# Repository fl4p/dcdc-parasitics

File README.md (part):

# parasitics — KiCad → FastHenry power-stage extractor

Extracts the half-bridge power-stage parasitic inductances and resistances
from a KiCad PCB for:

1. **Switch-node ringing** — the commutation-loop inductance that,
   with the FET Coss and Qrr, sets the SW overshoot and ring frequency.
2. **Gate-drive analysis** — compute gate-loop inductance and detect ringing
   issues. The gate loop overlaps the high-di/dt commutation path through the
   FET **source lead**, so that shared **common-source inductance (CSI)** feeds
   power di/dt back into the gate drive.
3. **Power-loss / efficiency modelling** — the extracted **resistances** are the
   copper contribution to the I²R budget, split **per switch** so
   the conduction loss can be weighted by each switch's duty (HS by D, LS by 1−D —
   the LS copper dominates at low duty). The loop carries current at two very
   different frequencies (switching frequency and HF ringing), so it has [two
   resistances](#two-resistances-hf-ring-vs-lf-conduction).

You give it the **switch-node net** and the **GND net**; everything else (HS/LS
FETs, Vin rail, gate nets, input caps) is auto-discovered from connectivity, with
overrides for every guess.

## Showcase

Half-bridge parasitics extracted from the open-hardware
[LibreSolar MPPT 2420 HC](https://github.com/LibreSolar/mppt-2420-hc) (4-layer
synchronous buck), rendered by `--svg`: each parasitic as a labelled coil, the
two **common-source source-leads in red**, the input-cap bank (the ported cap and
the greyed-out ones), and the auto-detected gate network (Rg). This is the
historical lead-inclusive fixture and is retained as an output-format showcase;
its numeric labels are not a current copper-only validation.

## How it works

Each extraction basis uses one FastHenry solve with multiple ports to obtain its
full mutual-inductance matrix. The baseline/full-loop extraction and the
`lead_mm=0` identity-matrix path need one solve. A non-identity matrix Cin request
may run three matched bases (`full_loop`, `cap_only`, and `switch_residual`) so
the producer can separate cap-side and switch-side copper without mixing gauges.

| Port | Across | Gives |
|------|--------|-------|
| `P_pwr` | nearest Cin — **MLCC** (Vin ↔ GND) | commutation-loop L, HF ring R |
| `P_ghs` | HS gate driver-end ↔ HS gate return | HS gate-loop L |
| `P_gls` | LS gate driver-end ↔ LS gate return | LS gate-loop L |
| `P_bulk` | nearest **bulk electrolytic** (Vin ↔ GND) | LF conduction-loop R |
| `P_hs` | Vin(bulk) → SW, via HS leads | HS conduction R |
| `P_ls` | SW → GND(bulk), via LS leads | LS conduction R |
| `P_probe_<name>` | any declared `REF.PAD` ↔ `REF.PAD` (opt-in, see `probe_ports`) | mount-loop L/R of that position |

### Electrostatic foundation (Palace)

Palace is the primary maintained electrostatic solver. The
`palace-electrostatic-pcb-gates-v2` path uses conformal tetrahedral volume
meshes, finite closed conductor terminals, explicit air/dielectric material
volumes, and a declared outer Dirichlet boundary that approximates
electrostatic infinity. That boundary is never treated as PE, chassis, a PCB
net, or SPICE node `0`; an outer-domain expansion ladder is mandatory.

`lib/palace_mesh.py` writes the qualified Gmsh fixtures. Real PCB geometry uses
`lib/palace_plc_mesh.py`: MeshPy nodes one global planar conductor/material
arrangement, that exact arrangement is reused at every geometry z-plane, and
triangular prisms receive a deterministic conformal tetrahedral split. It
rejects open/non-manifold shells, incomplete terminal/material coverage, and
nonpositive tetrahedral Jacobians, then emits first-order Gmsh 2.2 directly.
`lib/palace_build.py` binds the pinned source patch, CMake caches,
linked libraries, launcher, wrapper, and binary. `lib/palace.py` binds those
manifests to Palace JSON configs, runs the solver, gates an independently
ordered 17-digit terminal reaction-charge Maxwell matrix against Palace's
energy matrix, and preserves exact streams, resolved config, runtime metadata,
and execution identity. The qualification build also hard-checks explicit
`||b-Ax||/||b||` after every terminal solve. Mesh,
polynomial-order, and finite-domain ladders over the frozen air, enclosed-FR4,
and PCB-like fixtures must pass before any Fugu run. See
`docs/palace-electrostatic-qualification-plan.md`.

Production launches use a content-addressed user-space execution snapshot whose
config, mesh, launcher, solver, and helper bytes are validated before and after
the process. Ordinary runs select a bounded local resource class. Checkpointed
runs additionally require a finite resource decision and a canonical E5 ledger
attempt before launch; every attempt receives a fresh snapshot/output root, and
matrices are consumable only through the terminal ledger capability.

The complete 24-rung fixture ladder has passed. `extract_palace_mesh.py` runs
the two-interpreter KiCad adapter, preserves every named net and flashed no-net
item separately, retains NPTH holes as voids rather than terminals, and binds
PCB, dump, stackup/material policy, geometry controls, mesher, and output bytes:

```sh
PYTHONPATH=out/palace-qualification/venv/lib/python3.14/site-packages \
  python3 extract_palace_mesh.py board.kicad_pcb \
  --material 'Top Solder Mask=3.3' \
  --material 'Bottom Solder Mask=3.3' \
  -o out/palace-pcb-geometry
```

Material overrides are explicit assumptions, not validated values. A physical
Fugu model still requires source-bound P2 evidence, convergence ladders,
independent review, and actual material identification or bounded sensitivity.

### Diagnostic legacy (FasterCap)

`lib/fastercap.py` provides the independent 3-D electrostatic path: it closes
conforming 2-D triangle meshes into finite-thickness conductor surfaces, emits
closed interfaces between dielectric regions, writes self-contained FasterCap
panel files, and runs the headless solver through `$FASTERCAP`. Each deck has a
hashed sidecar manifest with stable solver labels. The runner returns a Maxwell
matrix only after exact label identity, normal termination, final automatic-norm,
per-RHS GMRES, live process-tree resource, raw reciprocity/passivity, strict
post-average passivity, and exact branch-reconstruction gates pass. Complete
matrices from failed or partial runs remain diagnostic-only. Manual fixed-`-m`/
fixed-`-t` probes use a separate API and never expose a qualified matrix. The
backend-neutral `lib/maxwell.py` validates matrix symmetry/passivity, converts
`Q = C_M V` into pairwise plus reference capacitors, reconstructs the original
matrix for an exact contract check, and emits a passive SPICE subcircuit. The
runner enforces a separate per-coupling reciprocity tolerance before returning
the symmetric average; FasterCap's `-a` tolerance controls refinement
convergence and is not reused as a reciprocity bound. Every invocation preserves
byte-exact content-addressed stdout/stderr and writes either a
`rejected_diagnostic` manifest or a `numerically_converged_diagnostic` manifest
under gate policy `fastercap-pcb-gates-v1`. Diagnostic convergence is not a
physical-model qualification.

This foundation is deliberately not wired into `extract_parasitics.py` yet.
`extract_capacitance.py` provides the first two-interpreter KiCad adapter: a
stdlib-only KiCad Python step dumps exact filled-zone contours in millimetres,
then system Python uses Shapely 2.1 constrained triangulation to close grouped
copper surfaces and converts every panel coordinate to FasterCap SI metres. For
example:

```sh
python3 extract_capacitance.py board.kicad_pcb \
  --group SWITCH=SW --group RETURN=PGND,GND \
  -o out/electrostatic-geometry

# Explicit opt-in reduced diagnostic representation
python3 extract_capacitance.py board.kicad_pcb \
  --group SWITCH=SW --group RETURN=PGND,GND \
  --representation effective-thickness \
  --effective-thickness-um 34 --anchor midplane \
  -o out/electrostatic-geometry-reduced
```

Generated names encode source, representation, material scope, and lifecycle,
for example `filled_zones_physical_air_only_diagnostic.lst` and
`filled_zones_effective_34um_midplane_air_only_diagnostic.lst`. Geometry metadata
uses a canonical content hash in its filename. Its fail-closed loader verifies
the filename/content ID plus the referenced deck, deck manifest, and reduction
provenance hashes. The deck manifest binds the same reduction provenance and its
hash; solver run manifests then bind the deck manifest plus all solver settings
and streams.

Both decks are geometry-development diagnostics, **not physical PCB capacitance
models**. They exclude tracks, pads, vias, and copper graphics and do not yet emit
the parsed stackup's dielectric interfaces. The only fixture-qualified reduction
is watertight closed 35 µm to 34 µm copper, midplane anchored, for overlapping
1 mm square parallel plates in air with a 100 µm source face gap and an explicit
pinned synthetic-fixture context. The reusable API marks any PCB/Fugu2 or
full-stackup use `outside_fixture_envelope`, fixes
`physical_validation_authorized=false`, and caps its lifecycle at
`numerically_converged_diagnostic`.

The content-addressed geometry manifest records limitations, PCB and contour-dump
hashes, KiCad version/interpreter, dump record count, areas, repair counts,
simplification error, minimum boundary segment, triangle/panel counts, source and
effective thicknesses, anchor, gap/displacement errors, qualification scope, and
artifact class. Use `--geometry-tolerance` (mm, default 0.001) as an explicit
panel-convergence knob; geometry that exceeds the area-error gate is rejected.

Start solver validation with the synthetic fixture:

```sh
python3 examples/fastercap_parallel_plate.py -o out/fastercap-parallel-plate
FASTERCAP=/path/to/FasterCap \
  python3 examples/fastercap_parallel_plate.py --run \
  -o out/fastercap-parallel-plate
```

The first command only emits inspectable geometry. The second writes
`capacitance.lib` only when every `fastercap-pcb-gates-v1` solver and matrix gate
passes. Unpatched FasterCap 6.0.7 macOS builds may emit
`Error: cannot retrieve the information about the free memory quantity`; the
fail-closed runner preserves a `rejected_diagnostic` manifest and returns no
matrix for those builds. The local macOS build uses Mach VM statistics for this
resource check and passes the real parallel-plate smoke test. See
`docs/fastercap-slice1-diagnosis.md`. A solver build that terminates without
diagnostics additionally reports plate-to-plate capacitance against the ideal
estimate; fringing means the ratio is not exactly one.

In the full-loop basis, both FET channels are shorted at the die plane
(`.equiv drain_die source_die`)
and each gate is closed to its source there, so `P_pwr` traces the full
`Cin → HS → SW → LS → GND → Cin` shoot-through loop and each gate loop shares that
FET's source lead. **CSI then falls out as the side-specific mutual**
`M(P_hs, P_ghs)` / `M(P_ls, P_gls)` — the shared source-lead partial inductance
that the gate driver actually sees. The older full-loop mutual is still recorded
as `csi_hs_loop` / `csi_ls_loop` in JSON for diagnostics. Whether the gate return
taps the die-source (**Kelvin**, CSI excluded) or the power-source pad
(**non-Kelvin**, full CSI) is encoded by where the gate-return node is placed
(default: non-Kelvin / worst case; force with `--hs-kelvin` / `--ls-kelvin`).

### Parallel input caps (`--cin-parallel N`)

By default `P_pwr` sits across the **single nearest** ceramic, which ignores the
other input caps that share the commutation current. For a pure-inductance port
matrix the parallel loop L is then lower than the single-cap number, so it usually
over-estimates SW-node overshoot -- but that is not a bound on the extracted
complex Z: copper R can put the parallel value above the single cap (see the two
references below). `--cin-parallel N` ports the **N nearest** input ceramics in the same
solve, so FastHenry returns their full mutual matrix, and the reduce step forms the
true effective 2-terminal commutation impedance under a common-voltage drive
(every cap pad pair at the same SW-node voltage, gates open):

```
Z_eff = 1 / (1ᵀ Zc⁻¹ 1)          (Zc = N×N cap-port submatrix)
```

which folds in every branch-to-branch mutual `Mᵢⱼ` exactly (not a naive `1/ΣLᵢ`),
solved as `Zc x = 1` (never an explicit inverse; `cond(Zc)` is reported and a
warning fires if it is ill-conditioned). The parallel-cap current split
`y = Zc⁻¹·1` is reported per refdes.

**The SW-peak loop L comes with two reference values. They are not bounds:**

| field | meaning |
|---|---|
| `L_loop_single` | nearest single cap alone |
| `L_loop_ideal` | all N caps ‖, treated as ideal shorts (copper only) |
| `L_loop_physical` | plateau-band result with the uniform per-cap series ESL/ESR supplied by `--cin-esl`/`--cin-esr` |

For a pure-inductance matrix, adding cap ESL can only raise the parallel L above
`L_loop_ideal`, and the parallel never exceeds the best single cap. Neither holds as a
bound on the extracted complex Z: copper R can lift the ideal-cap reduction above
`L_loop_single` (and the nearest cap need not have the lowest self-L), so treat the two as
references. Use `L_loop_physical` when cap ESL/ESR are known. `L_loop_physical` and the top-level `current_split` are evaluated at the selected
L plateau (default 5 MHz), not at `--ring-freq`. The reducer applies the same series
ESL/ESR at every point in `L_eff_sweep`, so that array contains the full effective
loop L/R sweep, including the point nearest the ring. It does not currently emit a
per-cap ring-frequency current split. The series-only cap term is a useful
above-SRF diagnostic; it is not a full C/ESR/ESL capacitor model. The loss tool
supplies that full model from dslib.

Without `--cin-esl`/`--cin-esr` the headline remains the ideal-cap copper-only
value. The two references always land in the report/JSON; `L_loop_physical` is set
only when a series ESL or ESR was supplied. Port polarity is fixed (always
Vin→GND) so a reversed cap cannot silently corrupt the mutuals; a spuriously-low
effective L still trips a warning.

**Cap selection.** Default is nearest-by-centroid-distance (deterministic, shown in
the manifest as `cin_select`); **bulk electrolytics are excluded by package/type**
(THT can/radial, `CP_`/`Elec`/tantalum/polymer footprints) — above their SRF they
can't source the tens-of-MHz edge. Classification is **by footprint, not value**, so
a 10–22 µF 1210 MLCC stays in the HF set while a small electrolytic stays out; the
per-refdes class is recorded in `cin_class`. Keep the bulk caps with
`--include-bulk-cin` (e.g. a low-frequency ripple-path study). Override selection
entirely with `--cin-loop-refs C17 C18 C9 C16`. If you request more caps than
exist, it warns and solves with what it found rather than silently clamping.

### Two resistances: HF ring vs LF conduction

The loop resistance is **not one number**, because it carries current at two
frequencies that see different copper and different reference caps:

| R | Freq | Anchored on | Used for |
|---|---|---|---|
| `R_loop` (ring) | ~MHz plateau | nearest **MLCC** (sources the edge) | SW-node ring Q / damping; skin-elevated |
| `R_hs` / `R_ls` (conduction) | ~DC fundamental | nearest **bulk electrolytic** | conduction I²R, split per switch |

At the 39 kHz switching fundamental the **MLCCs are ~open** and carry no conduction
current — the fundamental is sourced and returned by the **bulk electrolytics**. So
the conduction ports (`P_hs`/`P_ls`/`P_bulk`) anchor on the nearest bulk cap, not the
ceramic, and their R is read at the **lowest swept frequency** (skin depth ≫ copper
thickness there, i.e. the near-DC conduction value) rather than at the ring plateau.
`P_hs` drives Vin(bulk) → SW through the HS drain+source leads (the die short routes
it), so its self-R is that switch's true conduction copper; `P_ls` likewise for
SW → GND. The residual `R_loop_cond − R_hs − R_ls` is reported as the **SW-node
spreading R**. In the emitted `.SUBCKT`, `R_loop` is a single solved HF ring
resistance; its HS/LS `Rser` placement is only a damping distribution, split by
the LF `R_hs:R_ls` proportion. A reconstruction check warns if the per-side
conduction R exceeds the LF loop R (a port-polarity/SW-reference tripwire).
Boards with an **all-ceramic** input bank fall back to the nearest ceramic for the
conduction anchor (there the ceramics *do* carry the fundamental); the anchor
refdes and class are recorded in `cond_ref`.

Both `R_loop` and `R_hs`/`R_ls` are read at a single characteristic frequency (the ring
plateau and near-DC respectively). To get the **AC resistance at an arbitrary
frequency**, raise the skin sub-mesh (`--nwinc/--nhinc > 1`); the per-frequency
`L_eff_sweep` in the JSON then shows R rising across the band as skin/proximity effect
crowds the current.

#### Not two resistances — a curve (`cin_skin`)

"Ring plateau" was itself a compromise: the plateau is read at ~5 MHz, roughly a decade
**below** the band the SW ring actually decays in. Measured on Fugu2:

| band | loop R | vs the exported plateau |
|---|---|---|
| 39 kHz (f<sub>sw</sub>) | 1.41 mΩ | 0.45× |
| 3.9 MHz (exported `R_loop`) | 3.13 mΩ | 1.00× |
| **39 MHz (SW ring)** | **5.34 mΩ** | **1.70×** |
| 84 MHz | 5.48 mΩ | 1.75× — saturated |

The rise is **sub-√f and saturates** above ~20 MHz: once the skin depth falls below the
35 µm foil the current is already confined, so the textbook √f law over-predicts it. `L_loop`
is flat over the same span (3.20 → 3.16 nH) — only R moves.

A consumer that places a single R therefore damps its ring with the wrong number (the loss
deck was **−71 %** on the loop R at the ring). So the reduction also fits a series **Foster RL
ladder** to the swept solve and exports it as `cin_skin`: a set of (Rₖ, Lₖ) poles that add 0 Ω at
DC and Σ Rₖ at the ring. Consumers place it in series with the commutation leg on top of the
**DC-band** branch R (`cin_matrix.R_dc`) and get the whole curve, not two points. On Fugu2 five
poles track R(f) to 1.2 % from 39 kHz to 84 MHz.

The corners are FIXED (log-spaced) and only the pole resistances are solved, by **NNLS** — so the
fit is deterministic and Rₖ ≥ 0 by construction (a negative pole would be an *active* element).
`--ring-freq` sets the band it must be honest at (default 55 MHz) and `--skin-poles` the pole
count. The ladder is currently emitted only for a valid identity-basis matrix Cin
model (`--emit-cin-network --cin-network-model matrix` with pad-ideal
`--lead-mm 0` extraction). If the selected Cin basis cannot carry the fit, or if
the sweep (`--hf-freq`) never reaches the ring band, **no ladder is emitted** and
`cin_skin_unavailable_reason` says why. The rise is not extrapolated, and "no
ladder" must never be read as "copper is flat".

### Input-cap network (`--emit-cin-network`)

For the loss tool's **Cin ESR / input-ripple** model, `--emit-cin-network` ports the
**full input bank** (bulk + MLCC) individually (`P_cin_<ref>`, separate from the
MLCC-only HF-loop selection so `L_loop` is untouched). `--cin-loop-refs` selects
the caps used for the headline commutation-loop reduction;
`--cin-network-refs` independently restricts the full-bank network. The deprecated
`--cin-refs` spelling is only an alias for `--cin-loop-refs`.

Choose the copper model explicitly:

| requested model | behavior | intended use |
|---|---|---|
| `--cin-network-model matrix` | Preserves the full coupled-L cap-port matrix and may resolve to `cin_model.mode=matrix` or `matrix_with_sw_coupling`. With `lead_mm=0`, the accepted identity basis keeps all switch-side board-copper L in the matrix and emits `L_sw_element=0` by construction. | Production loss flow; required for heterogeneous banks such as the complete seven-cap Fugu2 bank. |
| `--cin-network-model scalar_trunk` | Legacy reduction to one shared Vin/GND trunk plus one private branch per cap: `L[i,i] = L_shared + Lb_i`, `L[i,j] ≈ L_shared`. | Compatibility and homogeneous-bank diagnostics only. |

The scalar reduction emits `cin_branches` and
`cin_L_shared`/`cin_R_shared`; its `_raw` counterparts preserve the unclamped
diagnostic decomposition. This topology cannot represent every passive coupled
matrix. The extractor therefore validates it and fails closed when it is invalid.
`--allow-scalar-cin` is an expert override that emits the legacy clamped model; it
does not make the approximation accurate. Consumers must dispatch on
`cin_model.mode` and `cin_model_valid`, not blindly consume the scalar fields.

Matrix mode emits `cin_matrix`, including its `basis`, cap refs, coupled L matrix,
`R_100k`, `R_dc`, realizability metadata, switch-copper ownership, and any resolved
switch coupling. The loss tool normally assembles the Cin SPICE text in memory and
includes the model/provenance header. If that text is instead supplied through a
persisted `cin_network.lib`, the reader uses its header to refuse stale, invalid,
or undispatchable networks; the extractor itself does not write this `.lib`.

Both models are **copper only** — parasitics stays parts-DB-free. The loss tool
enriches each `ref` with its datasheet C/ESR/ESL from dslib and builds the complete
`cin_network`. Copper branch resistance is distinct from dielectric ESR. In
matrix mode, `R_dc` supplies the base/conduction band and `cin_skin` adds the
frequency-dependent rise without double-counting switch-path resistance.

Meshing: tracks → filaments; copper pours → a gridded filament mesh clipped to the
real filled polygon (and to an ROI around the FETs/Cin, so far copper is skipped);
vias → vertical filaments; THT pads and FET leads → vertical stubs to a die plane.
Track widths come from KiCad; segment height is `--cu-thickness` (default 0.035 mm).
Nodes are interned by `(net, layer, snapped-xy)` so coincident same-net endpoints
merge, and every track/via/pad node is bonded to its pour (fixes fragmented
copper); a union-find prune keeps only port-reachable copper. `L = Im(Z)/2πf`,
`R = Re(Z)` read at a low-MHz plateau.

FET package inductance has a strict modeling boundary with the loss tool and
MOSFET SPICE models. The legacy `--lead-mm` path is an artificial die-plane
extension, not a physical bent-lead package model; use copper-only extraction for
loss when the MOSFET model already carries package leads. See
[docs/fet-package-boundary.md](docs/fet-package-boundary.md) for the full contract.

## Usage

```sh
python3 extract_parasitics.py PCB --sw SW_NET --gnd GND_NET \
        [--pitch 2.0 1.0] [--lead-mm 0] [--cu-thickness 0.035] [--lf-freq 1e3] [--vin NET] \
        [--cin-parallel 4 | --cin-loop-refs C17 C18 C9 C16] [--include-bulk-cin] \
        [--cin-network-refs C17 C18 C9 C16] \
        [--cin-esl 0.5 --cin-esr 3] \
        [--emit-cin-network --cin-network-model matrix|scalar_trunk] \
        [--hs-ref Q1 Q3 --ls-ref Q2] [--hs-gate NET --ls-gate NET] \
        [--parallel-fets lumped|per-device] \
        [--hs-kelvin] [--ls-kelvin] [--weld-tol 0.6] [--zone-mesh grid|polygon] \
        [--terminal-mode padland|single|finite|point] \
        [--extra-nets NET ...] \
        [--margin 8] [--svg] -o OUTDIR
```

The historical CLI defaults are `lead_mm=3`, `parallel_fets=lumped`, and
`cin_network_model=scalar_trunk`. They remain for artifact compatibility, not as
the recommended loss-flow combination. Set the package boundary and Cin model
explicitly in reproducible configs; the Fugu2 example below shows the current
lead-internal/matrix combination.

All CLI arguments can also be supplied from YAML:

```sh
python3 extract_parasitics.py --config fugu2-parasitics.yaml
```

YAML keys use the argparse destination names (`hs_ref`, `cin_parallel`,
`emit_cin_network`, etc.). Command-line arguments override YAML values, including
boolean options via `--no-svg`, `--no-hs-kelvin`, and the other `--no-*` forms.
`pcb` may be a local path or an HTTPS URL to a public `.kicad_pcb`; GitHub
`blob` URLs are converted to raw downloads automatically. Prefer a commit SHA in
the URL instead of a branch name for reproducible extraction.

For a local board in a git checkout, `pcb_rev: <commit or tag>` (`--pcb-rev`) with
`pcb_repo: <repository root>` (`--pcb-repo`) pins it the same way without publishing
anything: the board is read with `git cat-file <sha>:<path>` from `pcb_repo`, never
from the working copy, so another session's uncommitted edits to the board cannot
leak into the extraction. `<path>` is `pcb` relative to `pcb_repo`, computed from
the two strings alone. The repository is not discovered from the board's location,
because symlinks, nested `.git` dirs or files and `core.worktree` in the working copy
could change that discovery and so which committed file the same path meant. With a
full SHA, git's content addressing then makes the bytes independent of the working
copy; prefer a full SHA, since a tag or short hash is resolved in `pcb_repo`. Relative
`pcb` and `pcb_repo` resolve against the config's directory when the config gave them,
else against the cwd. A missing `pcb_repo`, a missing commit, a path outside
`pcb_repo` or a file absent from the commit fails hard; there is no fallback to the
working copy. `gate_copper.py` and `visualize_paths.py` honour it too; the full commit
lands in `meta.pcb_rev` and the in-commit path in `meta.pcb_rev_path`. The Fugu2
examples are pinned this way. `loop_inductance_guard.py` (kicad-design) passes the
board it gates on the command line, which replaces the config's `pcb`, its pin and
its `pcb_repo`, so a fresh guard
run extracts and gates exactly the file it was given -- pinned or not. Give it the
exported board (`git show <rev>:Fugu2.kicad_pcb > board.kicad_pcb`); handed the
working copy it gates the working copy. A fresh run and re-gating a saved
extraction (`--json`) both compare the extraction's `meta.pcb_sha256` with the
given board's hash and refuse a mismatch.

```yaml
pcb: https://github.com/org/repo/blob/<commit-sha>/hw/Fugu2/Fugu2.kicad_pcb
sw: SW
gnd: BuckGND
vin: Solar+
hs_ref: [Q1, Q3]
ls_ref: [Q2]
parallel_fets: per-device
lead_mm: 0  # package leads are owned by the vendor _L0 MOSFET model
cin_loop_refs: [C9, C16, C17, C18, C21, C22, C27]
pitch: [1.0]
emit_cin_network: true
cin_network_model: matrix
weld_tol: 0.6
zone_mesh: grid
terminal_mode: padland
margin: 8.0
cu_thickness: 0.035
lf_freq: 39000
out: out/
```

This example is the production Fugu2 loss-flow boundary: board copper is
extracted with `lead_mm: 0`, each parallel FET keeps its own ports, and the
lead-inclusive vendor MOSFET model owns package inductance. For a die-only model,
provide complete package-L ownership (the current automatic table may add only
drain L) or deliberately use a package-inclusive extraction with a lead-disabled
model; never combine both sources of package inductance.

`--hs-ref`/`--ls-ref` take **multiple** refdes for paralleled switches (e.g.
`--hs-ref Q1 Q3`). `--weld-tol` fuses same-net nodes within N mm (mesh
de-fragmentation, see below); `--margin` sets the pour-meshing ROI around the
FETs/Cin. `--zone-mesh grid` is the validated/default pour mesher. `--zone-mesh
polygon` is an experimental KiPEX-style cell-edge mesher for cross-checks; it is
not the production default because current simple-hb/Fugu2 checks under-read.
`--terminal-mode padland` is the validated/default pad-to-pour contact model.
`single` is a KiPEX-like one-mesh-node terminal, `finite` is an experimental
finite pad-contact model, and `point` is the legacy/debug pad-center stitch path
for A/B comparisons.

`--parallel-fets per-device` opts into the issue #5 extraction model for
paralleled switches: each physical FET keeps its own die/source/gate branch and
gets its own gate + switch-side ports (`P_ghs_Q1`, `P_hs_Q1`, ...). The default
is `--parallel-fets lumped`, which preserves the historical lumped parallel-FET
model and existing downstream behavior.

### `probe_ports` — measuring a position the derived ports do not cover

Every port above is *derived* from the discovered topology, so a component
mounted anywhere else on those nets — an added capacitor between SW and GND at
some particular pad pair, a snubber land — has no port and its **mount-loop
inductance can only be guessed**. `probe_ports` declares extra two-terminal
ports by `REF.PAD`, so that loop is extracted instead:

```yaml
probe_ports:
  cap_at_d9:    [D9.2, D9.3]     # the LS device tabs
  cap_q2_j3:    [J3.1, Q2.3]     # an as-built detour
  snubber_land: [R11.1, C8.2]    # the designed R11/C8 position
```

On the CLI: `--probe-ports 'cap_at_d9=D9.2:D9.3,cap_q2_j3=J3.1:Q2.3'`.

Each becomes `P_probe_<name>`, **appended** to `ports` (so `port_L` / `port_R` /
`port_R_dc` gain a row and column and nothing name-keyed shifts), plus a derived
block in `parasitics.json`:

```json
"probe_ports": {
  "cap_at_d9": {"label": "P_probe_cap_at_d9", "a": "D9.2", "b": "D9.3",
                "L": 1.9e-9, "R": 3.1e-4, "R_dc": 2.6e-4,
                "L_ring": 1.8e-9, "R_ring": 9.7e-4,
                "M_to_loop": 4.1e-10, "M_to_loop_port": "P_pwr",
                "pulled_new_copper": false}
}
```

Everything that can go wrong is a **hard error, never a silent skip** — unlike
`cin_loop_refs`, where a bogus refdes is simply dropped: unknown refdes, unknown
pad number, a pad that resolves to no copper contact (which would point-inject
and report a different inductance than the one asked for), a label or node-pair
collision (two `.external` on one node pair make FastHenry's `Zc` singular), and
a probe dropped as floating.

The one thing that cannot be made impossible is **measured, not assumed**:
`prune()` keeps only copper reachable from a port, so a probe reaching a
previously-unported region adds copper to the deck and can shift `L_loop`. Each
probe therefore carries `pulled_new_copper` (with `retained_nodes_added`), and
the run warns when any probe is flagged. A probe on already-ported copper reuses
that pad's existing terminal and adds nothing. **Verify by A/B**: run the same
config with `probe_ports` removed and diff `L_loop`, `L_loop_single`,
`L_gate_hs`, `L_gate_ls` and `cin_branches`.

`probe_ports` is refused on `cin_extraction_basis: switch_residual` — that basis
is a single-port residual gauge that rejects every extra solved port. In a
matrix-Cin run the internal residual leg runs without the probes (announced in
the log); the reported probe results come from the `full_loop` leg.

Example — Fugu2 (2-layer buck, paralleled HS, explicit HF cap bank):

```sh
python3 extract_parasitics.py .../Fugu2.kicad_pcb --sw SW --gnd BuckGND --vin Solar+ \
        --hs-ref Q1 Q3 --ls-ref Q2 --parallel-fets per-device --lead-mm 0 \
        --cin-loop-refs C9 C16 C17 C18 C21 C22 C27 \
        --emit-cin-network --cin-network-model matrix --pitch 1.0 -o out/
```

### `module` — an INTEGRATED-MODULE power stage (both FETs in one package)

Everything above assumes **discrete** switches: `fet_discovery` finds a high-side
FET whose drain sits on a non-GND rail and a low-side FET bridging SW and GND,
and `build_fet` closes each channel at a die plane `lead_mm` above the pad. That
die short is what makes the deck solvable at all. Hand it a board whose power
stage is a module — a TI TPSM33610S3Q, say — and it is correctly refused:

```
no high-side FET found on '/SW' (drain to a non-GND rail)
```

`probe_ports` does **not** substitute. A probe is an extra `.external` on copper
that is already in the deck; what is missing here is not a port but the galvanic
path. Without a closure the Vin copper and the GND copper are two separate
conductors, `P_pwr` spans them, and FastHenry answers (measured 2026-09-16):

```
Number of meshes:             0
Couldn't create sparse matrix, err 5          (exit 1, no Zc.mat)
```

Declare a `module:` block instead. It closes the input commutation loop at the
**package pads**:

```yaml
module:
  ref: U1
  vin_pads: ["3"]          # optional — auto-discovered from the vin net if omitted
  gnd_pads: ["10"]
  internal_closure: ideal_pad_plane
lead_mm: 0                 # required: a module has no declarable die plane
```

**`internal_closure` has no default, and never will.** The geometry from the
package pads to the dies is not public (TI's SNVSCS7E gives a land pattern and
layout guidance and no internal dimensions), so the tool refuses to choose it:

| `internal_closure` | solve | what `L_loop` means | extra fields |
|---|---|---|---|
| `ideal_pad_plane` | one `.equiv`, VIN pad group ↔ GND pad group | **board copper only**, internal contribution exactly 0 — a *lower bound* on the physical loop under the additive internal-L model (board-module mutual coupling neglected) | `module.L_loop_board`, `module.internal_L = 0` |
| `declared_internal` | **identical** — FastHenry has no lumped element | still board copper only | `module.L_loop_with_internal`, plus the required `internal_nh` and `internal_source` |

`L_loop` is board copper on **both** closures, on purpose: a declared internal
inductance is only ever added under its own name, so no consumer can read an
assumed path as an extracted one. `declared_internal` refuses a value without an
`internal_source` provenance string.

Every module declaration fails closed: a missing or misspelled key, an unknown
closure name, a refdes or pad that is not on the board, a pad that is on a
different net than declared, a closure that does not lie on the Cin loop, a
`P_pwr` joined through ideal links only, and a `P_pwr` whose terminals are not
connected at all (the "no loop" case above) are all hard errors. The closure pads
must terminate on real copper — a pour-mesh `overlap`, or `track_in_land` for a
rail routed with tracks and no pour — and a fabricated `proximity` bond is
refused unless the block declares `allow_proximity_bond: true`. The bond class
of every closure pad is recorded in `parasitics.json`.

Not available for a module, because none of it exists on the board: gate loops
and CSI (reported as `null`, never 0), the per-switch conduction split
(`r_hs`/`r_ls`), the plane-P `cap_only`/`switch_residual` bases, and
`parallel_fets: per-device`. `P_pwr`, `P_bulk`, `cin_branches` and `probe_ports`
all work unchanged.

Example — `examples/buck-tpsm33610-module.yaml`, TPSM33610S3Q on a 2-layer
9.1 × 12.6 mm breakout, pitch 0.25 mm:

```
L_loop = 3.63 nH (board copper only)   R_loop = 8.04 mOhm @ 3.9 MHz
cin trunk 2.90 nH   C2 (0603 HF) branch 0.84 nH   C1 (1206) branch 5.16 nH
```

### `extra_nets` — meshing copper the half-bridge topology does not touch

The meshed set is *derived*: `{--sw, --vin, --gnd}` plus the HS/LS gate nets, and
**nothing else**. That is exactly right for the commutation and gate loops, and it
makes whole regions of a board unreachable. On Fugu2 the buck's entire **output
power path** is outside it:

```
coil lug J6.1 (BflowS) -> Q5/Q6/Q7 -> F1 (Bat+ -> BT+) -> J9.1 (BT+)
return:  J9.2 (GND) -> R26 (0.5 mOhm shunt) -> BuckGND
```

`BflowS`, `Bat+`, `BT+`, `GND` (a **different** net from `BuckGND` — R26 straddles
them) and `T_HV+` are never meshed, so a `probe_ports` entry on any of them dies
with

```
probe_ports: out_coil_bflow: pad J6.1 (net 'BflowS') resolved to NO copper
contact on any of its layers (layer 0: no_same_net_zone_mesh; ...)
```

That refusal is **correct** — the alternative is a bare pad-centre node that
point-injects the current and reports a loop inductance nobody asked for. What was
missing was copper, not permission. `extra_nets` supplies it:

```yaml
extra_nets: [BflowS, "Bat+", "BT+", GND, "T_HV+"]
probe_ports:
  out_coil_bflow: [J6.1, C10.1]     # both on BflowS
```

On the CLI: `--extra-nets BflowS Bat+ BT+ GND T_HV+`. Net names are passed as
separate argv items, never packed into one string — a KiCad net name may contain
`,`, `:` and `=`.

**Extra nets do NOT extend the meshing ROI.** `--margin` stays the single ROI
authority, for two reasons: a net like `GND` spans the whole outline, so an
auto-grown ROI would silently mesh the entire board at the one place this tool has
a hard cost cliff; and moving the ROI moves the *power-net* pour mesh too, so
adding a diagnostic net would shift `L_loop`. Instead the tool **says so** — a
requested net whose pour the ROI never reaches is a hard error naming the margin
that would first reach it:

```
extra_nets: the following net(s) got NO pour mesh — the meshing ROI
(21.0, 31.7) .. (69.5, 96.7) mm does not reach their filled copper:
  - 'Bat+': 456 track/via node(s) but no pour mesh; its pour spans
    (58.5, 75.2) .. (73.7, 89.2) mm; --margin >= 10.8 mm would first reach it
    (currently 8 mm)
```

Note the predicate is the **pour** mesh, not node count: only `add_zones` is
clipped to the ROI, so a net whose fill is 30 mm away still arrives with hundreds
of track and via nodes while a pad-land terminal has nothing to bond to.

Everything else that can go wrong is a hard error too, never a silent drop
(unlike `cin_loop_refs`): an unknown net name — with a `did you mean` suggestion —
and a net with no filled zone anywhere on the board, where no margin can ever
help.

**Reachability, and why an extra net is usually an island.** Extra nets are
galvanically separate from the switching cell: the back-flow FETs, the fuse and
the shunt in between are *components*, and the extractor models neither. So:

- an extra net with **no port** on it is dead copper. `prune()` keeps only
  port-reachable copper, so it is meshed and then dropped from the deck entirely
  — it costs geometry time and appears in no result. The run **warns**, with the
  node count.
- an extra net **with** a probe port on it survives `drop_floating_ports` through
  a narrow, opt-in allowance: both endpoints must be in ONE component, and every
  node of that component must be on a declared extra net. The NaN condition the
  guard actually protects against — two endpoints on two *different* conductors —
  is never relaxed, for any net. (FastHenry solves disjoint conductors fine;
  measured on two 10 mm × 1 mm traces at 1 MHz, it returns a finite symmetric 2×2,
  6.99 nH self and 1.66 nH mutual.)
- that copper is then **in the solved deck**, so it adds mutual coupling to the
  commutation loop. `L_loop` from such a run is **not** comparable with the same
  config without `extra_nets`; the existing `probe_ports[].pulled_new_copper`
  flags say which probe pulled it in.

Provenance lands in `parasitics.json` under `meta.extra_nets` — per net: the
`nodes` / `zone_nodes` meshed, how many were `retained` after the prune, whether
it is `ported` and `isolated`, its copper `bbox` / `zone_bbox`, and
`margin_required_mm` — plus the run's `roi`, `margin`, and
`roi_policy: extra_nets_do_not_extend_roi`. `report.md` carries a banner
separating the nets that are in the solved deck from the ones that were pruned
back out. Both are emitted **only** when the option was used, so a run without it
produces byte-identical artifacts.

### Interactive path viewer

`visualize_paths.py` emits a standalone HTML/SVG viewer for inspecting the copper
that participates in the extracted parasitic paths. The first view is the
gate-drive loop: HS/LS paths can be toggled independently, with separate toggles
for driver-output copper, FET-gate copper, source-return copper, source-lead CSI
markers, parts, and top/bottom copper layers.

```sh
python3 visualize_paths.py .../mppt-1210-hus.kicad_pcb \
        --sw "/DCDC power stage/SW_NODE" --gnd GND \
        --vin "/DCDC power stage/SOLAR+" --hs-ref Q1 --ls-ref Q4 \
        -o out/gate-loop-viewer.html
```

It also accepts viewer-specific YAML using its argparse destination names:

```yaml
pcb: path/to/board.kicad_pcb
sw: /DCDC power stage/SW_NODE
gnd: GND
vin: /DCDC power stage/SOLAR+
hs_ref: [Q1]
ls_ref: [Q4]
margin: 8.0
out: out/gate-loop-viewer.html
```

```sh
python3 visualize_paths.py --config viewer.yaml
```

Use only the viewer arguments shown by `visualize_paths.py --help`; unknown keys
fail closed. If `out` points to a directory, the viewer writes
`gate-loop-viewer.html` inside it.

It uses the same `fet_discovery.py` topology logic as the extractor and re-execs
itself under KiCad's bundled Python if `pcbnew` is not importable from the shell
Python. The output is self-contained and can be opened directly in a browser.

Multiple `--pitch` values run a mesh-convergence sweep (report drift; finest used
for the artifacts). Example (the MPPT test board — a coarse pair for a quick drift
check):

```sh
python3 extract_parasitics.py .../mppt-2420-hc.kicad_pcb \
        --sw "/DC/DC/SW_NODE" --gnd GND --pitch 3.0 2.0 -o out/
```

Runtime note: finer meshes take longer on this 4-layer example. Each pitch
halving creates roughly 4× as many pour filaments per layer, and FastHenry's
single-threaded solve scales super-linearly. On this board, `--pitch 2.0`
finishes in seconds while `--pitch 1.0` can take 10+ minutes. Use a coarse pair
for a quick convergence check; add `--pitch 1.0` when the converged value is
worth the wait, or reduce `--margin` to trim the meshed ROI. This affects runtime
only.

The `--pitch 2.0` result reproduces the historical lead-inclusive fixture's
~8.5 nH loop value; that number is not the copper-only package boundary.

### Outputs (`OUTDIR/`)
- **`parasitics.lib`** — `.SUBCKT pwrstage VIN SW GND HSG LSG HSKEL LSKEL`. CSI is a
  **shared source-lead branch** (`Lscs_hs`/`Lscs_ls`): drive the HS gate between
  `HSG` and `SW` for non-Kelvin (CSI in the loop) or between `HSG` and `HSKEL` for
  Kelvin (CSI excluded). Add your Cin across `VIN–GND` and device models for a
  gate-drive/DPT or SW-overshoot sim.
- **`parasitics.json`** — named parasitics + full port L/R matrix + provenance.
  `meta.pcb_sha256` records the SHA-256 of the resolved `.kicad_pcb` input so
  downstream tools can detect stale extraction artifacts; `meta.pcb_rev` is the
  full commit when the board was pinned with `pcb_rev`, else null (`meta.pcb_rev_path`: the
  board's path inside that commit). When extracted through
  `--config`, `meta.extract_config_sha256` records that YAML file's SHA-256 too.
  CSI fields: `csi_hs` / `csi_ls` are side-specific source-lead mutuals used in
  the emitted subckt; `csi_hs_loop` / `csi_ls_loop` are the full-loop mutuals for
  diagnostics.
  Conduction fields: `r_hs`, `r_ls` (per-switch conduction R), `r_loop_cond` (LF
  loop R), `r_sw` (SW spreading residual), `r_cond_freq` (the freq they were read
  at), and `cond_ref` (`{ref, cls}` — the bulk cap they anchor on). With
  `--emit-cin-network`, `cin_model`/`cin_model_valid` select the copper contract.
  Matrix modes use `cin_matrix` (`basis`, `refs`, coupled `L`, `R_100k`, `R_dc`,
  switch-coupling and realizability metadata); a valid identity basis owns all
  switch-side board L and has `L_sw_element=0`. `cin_skin` carries the optional
  Foster RL correction on top of `R_dc`, while `cin_skin_unavailable_reason`
  explains why no ladder was emitted. Legacy scalar mode uses `cin_branches` +
  `cin_L_shared`/`cin_R_shared`; the corresponding `_raw` fields are diagnostics,
  not an alternative consumer contract. The loss tool dispatches on the model
  metadata, fills each cap's datasheet C/ESR/ESL from dslib, and assembles the
  matching `cin_network`.
- **`report.md`** — table + a topology sketch of where CSI sits.
- **`schematic.svg`** (with `--svg`) — a standalone half-bridge drawing of the
  extracted network: each parasitic as a labelled coil, the two common-source
  source-leads in red, and the input-cap bank showing which caps the model ported
  (parallel legs with their current split) vs. board caps left out of the loop.
  The discrete **gate network** (series Rg and any anti-parallel diode, auto-found
  on the gate net) is annotated for context — copper-only FastHenry does not model
  it, so the coil's `R` is the trace resistance (`Cu`), distinct from the gate Rg.
- **`cin_network.svg`** (with `--svg --emit-cin-network`) — an LF drawing of the
  shared-trunk/per-cap diagnostic decomposition. If `cin_model` resolves to a
  matrix and rejects the scalar decomposition, this SVG is diagnostic only; use
  `cin_model`/`cin_matrix` rather than treating the drawing as the emitted model.

## Layout

`extract_parasitics.py` at the repo root is the extraction CLI. It runs the
two-interpreter pipeline: the geometry step (`lib/kicad_geom.py`) under KiCad's
python, the solve/reduce/emit under system python. `visualize_paths.py` is the
standalone HTML path-viewer exporter. `gate_copper.py` writes one SVG per
gate-drive loop (HS, LS): every track, via, pour fill and pad on the driver,
gate and source-return nets around the FETs, one colour per copper layer. Use it
to check that the extraction meshes the right gate geometry and to spot missing
vias, thin necks and detours. It takes the same YAML as the extractor
(`python3 gate_copper.py --config examples/fugu2-cu.yaml`, with `out:` set) and
ignores the extraction-only keys; `--split-fets` draws paralleled devices
separately.

```
extract_parasitics.py   # FastHenry CLI (orchestrates the two interpreters)
extract_capacitance.py  # KiCad filled zones -> FasterCap diagnostic deck
extract_palace_mesh.py  # complete KiCad PCB -> source-bound Palace PLC mesh
visualize_paths.py      # -> standalone HTML PCB path viewer
gate_copper.py          # -> one SVG per gate-drive loop, colour per layer
lib/
  kicad_geom.py         # pcbnew -> multiport FastHenry .inp (KiCad python)
  kicad_fastercap_dump.py # stdlib + pcbnew -> exact contour JSON
  kicad_fastercap.py    # contour JSON -> constrained SI-unit conductor surfaces
  kicad_palace_dump.py  # stdlib + pcbnew -> complete copper/drill/census JSON
  kicad_palace.py       # complete dump + stackup -> closed volume primitives
  fet_discovery.py      # auto-ID FETs / Vin / gate nets / Cin / gate network
  extra_nets.py         # opt-in extra meshed nets: guards + provenance
  solve_reduce.py       # run fasthenry, parse Zc.mat -> named parasitics
  fastercap.py          # diagnostic surface-BEM path
  palace_mesh.py        # closed fixture geometry -> conformal Gmsh volume mesh
  palace_plc_mesh.py    # PCB volumes -> exact extruded PLC tetrahedral mesh
  palace.py             # Palace config/run/raw Maxwell qualification
  palace_build.py       # Palace source/build/runtime provenance
  maxwell.py            # validate/convert Maxwell C -> branches/SPICE
  emit.py               # -> parasitics.lib / .json / report.md
  emit_svg.py           # -> schematic.svg
test/                   # pure-layer tests (pytest; numpy/scipy where needed)
docs/                   # rendered example(s)
```

Several `lib/` modules also have a small `__main__` for standalone/debug use
(e.g. `python3 lib/emit_svg.py parasitics.json > schematic.svg`).

## Requirements & config

- **KiCad** (pcbnew) — the geometry step runs under KiCad's bundled python. Path
  via `$KICAD_PY` (default: the macOS KiCad.app bundled interpreter).
- **FastHenry** — path via `$FASTHENRY` (default `~/dev/vendor/FastHenry2/bin/fasthenry`).
  Build the FastFieldSolvers fork; on a modern clang toolchain use e.g.
  `CFLAGS='-O -DFOUR -m64 -std=gnu89 -fcommon -Wno-implicit-function-declaration
  -Wno-implicit-int -Wno-return-type -Wno-deprecated-non-prototype' make`.
- **Palace** — primary electrostatic solver, pinned and built separately from
  `awslabs/palace`; set `$PALACE` or pass `--executable`, and pass the required
  content-addressed build attestation with `--build-manifest`, to the Palace
  fixture study. The qualification build and policy are documented in
  `docs/palace-electrostatic-qualification-plan.md`.
- **FasterCap** — optional diagnostic legacy; set `$FASTERCAP` or pass
  `--executable` to its parallel-plate example. Tested with FasterCap 6.0.7.
  The core FastHenry extraction does not require either electrostatic solver.
- Python 3 dependencies from `requirements.txt`:

  ```sh
  python3 -m pip install -r requirements.txt
  ```

  This installs NumPy and PyYAML for extraction/config parsing, SciPy for the
  matrix skin-ladder fit and density solver, Shapely 2.1 for system-Python
  polygon conditioning, MeshPy for constrained PCB PLC topology, Gmsh for
  fixture meshing and mesh-content validation, and Matplotlib
  for the default mesh viewer and heatmaps. The KiCad dump step does not import
  these packages.
  The core extraction survives a viewer-render failure, but
  `mesh/mesh.html` will be skipped when Matplotlib is unavailable.

## Paralleled switches

`--hs-ref`/`--ls-ref` accept several refdes (e.g. `--hs-ref Q1 Q3`). By default
(`--parallel-fets lumped`) each paralleled FET contributes its own drain and
source lead stubs; the dies are tied to one node, so between the rails you get
the drain leads in parallel and the source leads in parallel, and **FastHenry
solves the real current split** — the lower-inductance (shorter) device carries
more current, so `L_loop` is the impedance-weighted parallel value, *not* a
naïve `L/2` and *not* the shorter-path-only value. Caveats:

- **Ideal channel.** Tying the dies models `Rds_on = 0`, so the split is set by
  copper/lead impedance alone. That is the dominant term at the commutation edge
  (good for SW-peak/di-dt) but ignores the `Rds_on` that equalises the split at
  low frequency — `L_loop` is the HF, channel-ideal value.
- **CSI is the parallel combination in lumped mode.** The reported `CSI_hs` is
  the paralleled source leads, but each device's gate-return current flows
  through *its own* source lead, so the CSI a single gate driver feels is
  **higher** than reported. In lumped mode only the first FET's gate loop is
  ported, for compatibility with old outputs.
- **Per-device mode is opt-in.** With `--parallel-fets per-device`, parallel
  dies are no longer `.equiv`'d together and each physical FET gets separate
  gate + switch-side ports. `parasitics.json.parallel_devices` carries per-ref
  `L_gate`, `R_gate`, `csi`, `csi_loop`, `L_switch`, and `r_switch`; the side-level
  `L_gate_hs`/`csi_hs` scalars remain as max-per-device compatibility values
  for older consumers. The loss deck consumes the per-ref gate/CSI values directly
  and treats `L_switch` as total per-device switch-path self-L. Because per-device
  CSI is already placed as `Lscs`, the loss deck derives a non-negative drain-side
  residual from `L_switch - csi` and adds only the excess over the lowest residual
  on that side. This preserves total switch-path imbalance without adding the
  source contribution twice.

## Limitations / notes

- FastHenry is magnetoquasistatic (L/R only) — Coss resonance stays in SPICE; the
  emitted subckt is parasitics-only, combine with device models downstream.
- **Mesh de-fragmentation.** Nets with no pour (gate) or split power fills can
  fragment (a track ending inside a pad, touching fills) → an all-NaN solve.
  `Model.weld(--weld-tol, default 0.6 mm)` fuses same-net+layer nodes within that
  radius (< pour pitch, so it never welds across the mesh grid); vias are modelled
  for every net. Needed for 2-layer boards; raise `--weld-tol` if a port stays
  disconnected (the geometry step prints node/segment/port counts).
- **Cap auto-select can mis-pick.** Nearest-by-centroid may land on a far or
  poorly-connected cap (on Fugu2 it chose a 1 µF 13 mm away on an isolated plane
  pocket). Pin the real HF ceramics with `--cin-loop-refs …` when the auto pick looks
  wrong or the loop won't close.
- **Package boundary.** `--lead-mm` is a legacy artificial die-plane riser, not a
  physical bent-lead package model. Use exactly one package-inductance owner:
  `lead_mm=0` plus a lead-inclusive vendor model, `lead_mm=0` plus explicit and
  complete package-L ownership for a die-only model, or a deliberate
  package-inclusive extraction plus a lead-disabled model. Never add a
  lead-inclusive SPICE model on top of a lead-inclusive extraction. With
  paralleled switches, `lead_mm=0` requires `--parallel-fets per-device` so
  distinct pad lands are not ideal-shorted together. See
  [docs/fet-package-boundary.md](docs/fet-package-boundary.md). In particular,
  the current loss deck's automatic package table may provide only drain L;
  source/gate L still require a model or explicit overrides.
- Gate-return **Kelvin detection is not automatic** — defaults to non-Kelvin
  (worst-case CSI); set `--hs-kelvin`/`--ls-kelvin` if the layout Kelvin-senses.
- FET/gate discovery is heuristic; the printed topology shows what was detected —
  override with `--hs-ref/--ls-ref/--hs-gate/--ls-gate/--vin` if wrong.
- Solve time is set by mesh density (FastHenry's iterative solver, **single-threaded**
  with a super-linear solve): a ~2 mm pour pitch on a small 2-layer board is a few
  thousand filaments and solves in minutes; drop to `--pitch 3` for a quick look,
  `--pitch 1` (slower) when you need accuracy. **Cost scales steeply with pitch and
  layer count** — each pitch halving is ~4× the pour filaments *per layer*, so
  `--pitch 1` on a 4-layer board (e.g. mppt-2420-hc) is a 10+ minute run. Shrink the
  meshed ROI with a smaller `--margin`, or run a coarse pitch / single pitch, when it
  drags.

## Tests

Tests for the pure layers (no KiCad/FastHenry) live in `test/`. Install the
runtime requirements above plus pytest, then run the complete suite:

```sh
python3 -m pip install pytest
python3 -m pytest -q test
```

The suite covers YAML/config guards, reduction and Cin-matrix contracts,
frequency-dependent skin fitting, SVG/report rendering, weld/via behavior, and
the DC density solver. The pcbnew/FastHenry geometry+solve path is covered by
running on the real boards below.

## Validation

- Historical `mppt-2420-hc` lead-inclusive fixture (4-layer buck; SW
  `/DC/DC/SW_NODE`, HS `Q1`, LS `Q2`): loop L ≈ 8.5 nH, CSI_hs ≈ 0.71 nH,
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
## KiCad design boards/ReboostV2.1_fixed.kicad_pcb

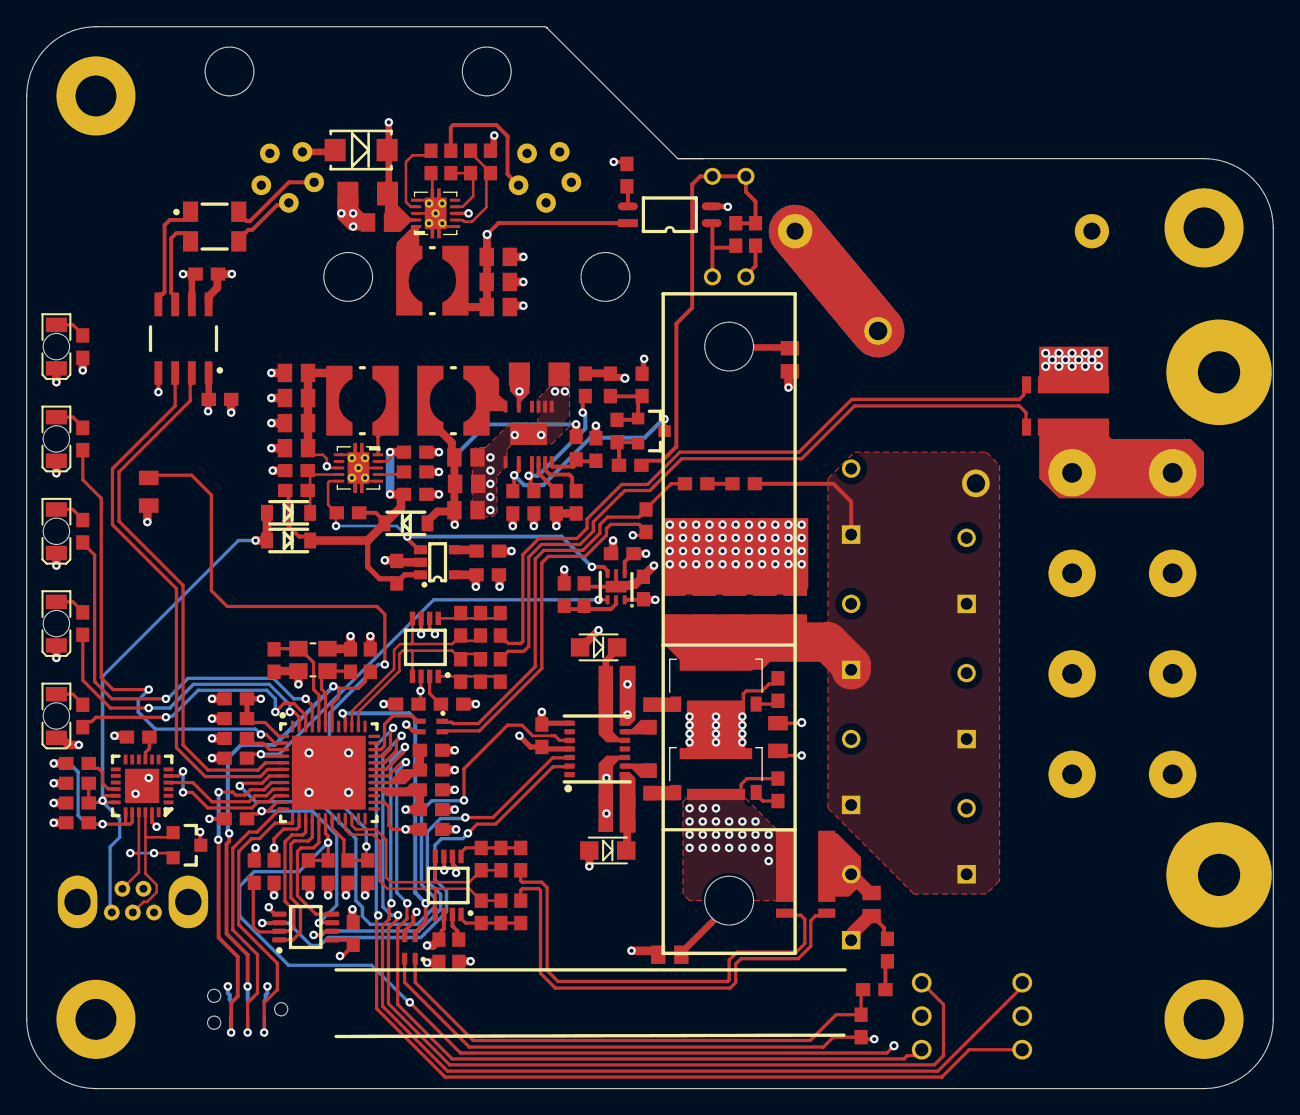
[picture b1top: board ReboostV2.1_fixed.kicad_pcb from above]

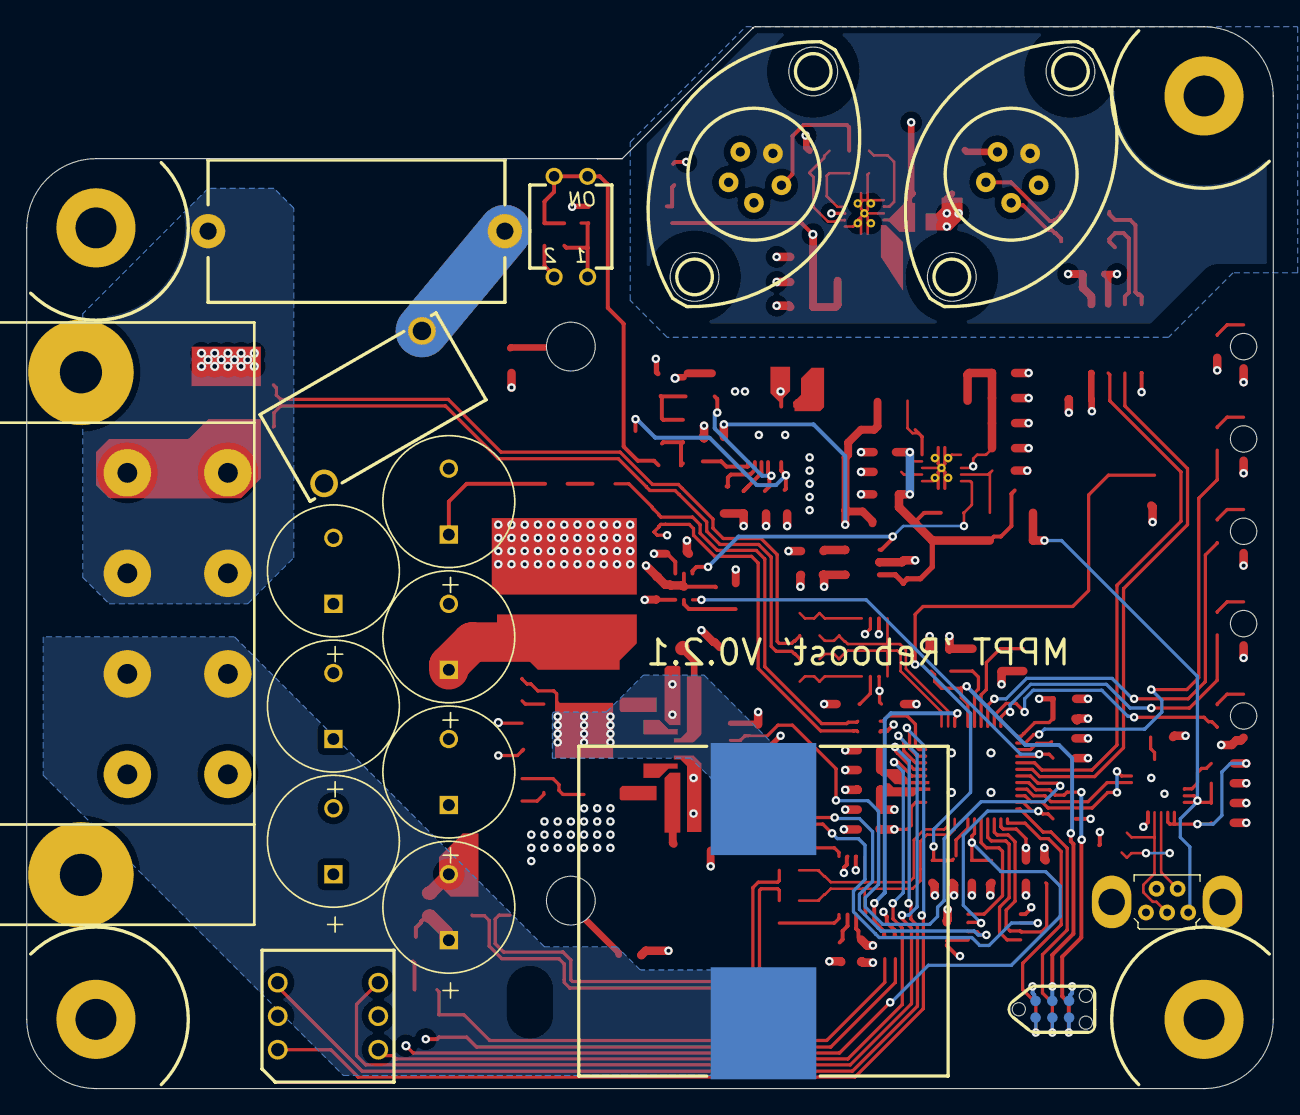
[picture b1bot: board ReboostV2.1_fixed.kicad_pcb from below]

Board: 4 copper layers, 94.5 x 80.5 mm, 177 parts (17 on the bottom side), 111 nets.

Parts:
C1_IHS, C1_ILS, C4_IHS, C4_ILS: 1nF; C0603
C2_IHS, C2_ILS, C3_IHS, C3_ILS, C6, C9, C13, C15, C16, C17, C18, C20, C21, C31, C39, C42, C45, C51, C54, C59, C60, C61: 100nF; C0603
C5, C7, C8, C12, C14, C19, C30, C40, C52, C56, C67: 2.2uF; C0603
C10, C11: 15pF; C0603
C22, C23, C24, C25, C26, C28, C34: 100uF; WCAP-ATUL_10x20x5x0.6
C27, C29, C35, C43: 100nF; C-0805
C32, C33, C36, C37, C38, C44, C64: 1uF; C-1206
C41, C46, C53, C58, C62, C65, C66: 10uF; C-0805
C47, C55, C57: 10nF; C0603
C48, C49, C50: 4.7uF; C-0805
D1: SP0502BAHTG; SOT23
D2, D3: SS110L; SUB-SMA
D4: HMHA2801; FSOP4
D5, D6, D7: MMSD701T1G; SOD123 - B
D8: SMAJ58A; SMA
F1: Fuse Holder; Fuse5x20TH
J1: Header 1x4; PC 4/ 4-G-7,62
J2: USB-B-MINI-VERT
J4: TagConnect 6p NL; TC2030-IDC-NL
J8, J9: CAN_BUS-Deutsch_ASL206-05SD-HE; ASL206-05SD-HE
L1: 2uH, 10A; 744710210
L2: 68uH, 11.2A; WE-HCF_2920
L3, L4, L5: 150uH 0.42A; WE-TPC 4828, MH
L6: 800Ohm; WE-CNSW_1812
L7_VHS, L7_VLS: 90Ohm; WE-CNSW_0805
LED1, LED4, LED5: GRN; WL-SMRW_1206 cylindrical_Reverse use
LED2, LED3: RED; WL-SMRW_1206 cylindrical_Reverse use
MP1, MP2, MP3, MP4, MP5, MP6: M2.5x2mm; 9774020151
Q1, Q2: GS61008T
Q3: MMBT5401LT1G; SOT-23
R1, R2, R3, R4, R5: 330R; 0603
R6_IHS, R6_ILS: 0.005R; 2512-L-4T
R7_IHS, R7_ILS, R9_IHS, R9_ILS: 1K; 0603
R8_IHS, R8_ILS, R10_IHS, R10_ILS, R35, R47: 47k; 0603
R11, R16, R17, R24, R32, R36, R42, R44, R45, R49_VHS, R49_VLS, R50: 10K; 0603
R12_VHS, R12_VLS: 120K; 0603
R13_VHS, R13_VLS: 180K; 0603
R14, R15: 10k; 0603
R18, R19, R28: 100K; 0603
R20, R21: NTC-100K; R0805
R22, R27: 2R; 0603
R25, R34: 750K; 0603
R26: 470K; 0603
R29: 470; 0603
R30: 20K; 0603
R31: 100R; 0603
R33: 130K; 0603
R37, R38, R40, R53: 200K; 0603
R39, R41: 0R; 0603
R48: 12K; 0603
S1: 418127270902
S2: 428527320916; 42852732091x_16p
U1_IHS, U1_ILS: LTC6362; MSOP8
U2: CP2104-F03-GM; QFN24
U3: STM32G474; QFN48
U4: 74LVC2G08; TSSOP8
U5: Si8273; DFN-14
U6: ISO1044; SO-8
U7: LM5165XDRCT; PWSON10
U8: LTC3639EMSE; MSE1612
U9: LM5165YDRCT; PWSON10
U10: LP2985AIM5-3.3; SOT-23-5
U11: TPS7A2501; WSON-6
X1: 16MHz; 7M

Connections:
5Vcan: C39.2, C46.2, C58.2, C62.2, D4.1, L3.2, U6.8, U7.8
CANH: J8.2, J9.2, L6.3
CANL: J8.3, J9.3, L6.2
CANRX: U3.43, U6.3
CANTX: U3.44, U6.2
CGND: C39.1, C43.1, C44.1, C46.1, C47.1, C58.1, C62.1, D8.1, J8.4, J9.4, R29.1, R31.1, U6.7, U7.3, U7.5, U7.10, U7.CP
DREN: U3.42, U5.5
D_N: D1.K1, J2.2, U2.4
D_P: D1.K2, J2.3, U2.3
GND: C2_IHS.1, C2_ILS.1, C3_IHS.1, C3_ILS.1, C5.1, C6.1, C7.1, C8.1, C9.1, C10.1, C11.1, C12.1, C13.1, C14.1, C15.1, C16.1, C17.1, C18.1, C19.1, C20.1, C21.1, C22.2, C23.2, C24.2, C25.2, C26.2, C27.1, C28.2, C29.1, C30.1, C31.1, C32.1, C33.1, C36.1, C37.1, C38.1, C41.1, C42.1, C45.1, C48.1, C49.1, C50.1, C51.1, C52.1, C53.1, C54.1, C55.1, C56.1, C57.1, C59.1, C60.1, C64.1, C65.1, C66.1, C67.1, D1.A, D4.3, J1.0, J2.0, J2.5, J4.5, L7_VHS.3, L7_VHS.4, L7_VLS.3, L7_VLS.4, LED1.1, LED2.1, LED3.1, LED4.1, LED5.1, Q2.S, R6_IHS.1, R6_ILS.1, R15.2, R16.1, R17.1, R20.1, R21.1, R32.1, R34.1, R36.1, R37.1, R39.1, R40.1, R42.1, R48.1, R49_VHS.2, R49_VLS.2, R50.1, S1.2, S2.C, U1_IHS.6, U1_ILS.6, U2.0, U2.2, U3.49, U4.4, U5.4, U5.12, U6.4, U8.6, U8.7, U8.8, U8.16, U8.17, U9.3, U9.5, U9.10, U9.CP, U10.2, U11.5, U11.7, X1.0
HI: U4.7, U5.3
HS: U3.33, U4.1
HSEN: R16.2, U3.34, U4.2
HSG: R22.1, U5.9
HSS: C40.1, C61.1, L2.1, Q1.S, Q2.D, R24.1, U5.8
ID0: S2.1, U3.16
ID1: S2.2, U3.17
ID2: S2.4, U3.18
ID3: S2.8, U3.19
LED0: R5.2, U3.4
LED1: R4.2, U3.3
LED2: R3.2, U3.2
LED3: R2.2, U3.47
LO: U4.3, U5.2
LS: U3.32, U4.5
LSEN: R17.2, U3.38, U4.6
LSG: R27.1, U5.13
NetC1_IHS_1: C1_IHS.1, R7_IHS.2, R8_IHS.1, U1_IHS.1
NetC1_ILS_1: C1_ILS.1, R7_ILS.2, R8_ILS.1, U1_ILS.1
NetC3_IHS_2: C3_IHS.2, U1_IHS.2
NetC3_ILS_2: C3_ILS.2, U1_ILS.2
NetC4_IHS_1: C4_IHS.1, R9_IHS.2, R10_IHS.1, U1_IHS.8
NetC4_ILS_1: C4_ILS.1, R9_ILS.2, R10_ILS.1, U1_ILS.8
NetC7_2: C7.2, U2.16
NetC10_2: C10.2, U3.5, X1.1
NetC11_2: C11.2, U3.6, X1.2
NetC14_2: C14.2, C15.2, U3.20
NetC30_2: C30.2, C59.2, D2.2, U5.14
NetC40_2: C40.2, C61.2, D3.2, U5.10
NetC47_2: C47.2, U7.4
NetC51_2: C51.2, U8.10
NetC55_2: C55.2, U9.4
NetC57_2: C57.2, U10.4
NetD4_2: D4.2, R29.2
NetD4_4: D4.4, R41.1, S1.1
NetD5_2: D5.2, R35.1, R42.2, U9.7
NetF1_1: F1.1, L1.2
NetL3_1: L3.1, U7.1
NetL4_1: L4.1, U8.1
NetL5_1: L5.1, U9.1
NetL6_1: L6.1, U6.5
NetL6_4: L6.4, U6.6
NetLED1_2: LED1.2, R1.1
NetLED2_2: LED2.2, R2.1
NetLED3_2: LED3.2, R3.1
NetLED4_2: LED4.2, R4.1
NetLED5_2: LED5.2, R5.1
NetQ1_G1: Q1.G1, R24.2
NetQ1_G2: Q1.G2, R22.2
NetQ2_G1: Q2.G1, R50.2
NetQ2_G2: Q2.G2, R27.2
NetQ3_1: Q3.1, R38.1, R53.2
NetQ3_2: Q3.2, R26.1, R37.2, R53.1
NetQ3_3: Q3.3, R34.2, U8.14
NetR11_1: R11.1, U2.9
NetR12_VHS_1: R12_VHS.1, R13_VHS.2
NetR12_VLS_1: R12_VLS.1, R13_VLS.2
NetR15_1: R15.1, U3.46
NetR25_1: R25.1, R32.2, U8.12
NetR28_1: R28.1, R30.2, U7.7
NetR30_1: R30.1, R31.2, U7.9
NetR33_1: R33.1, R36.2, U8.9
NetR38_2: R38.2, R39.2, R41.2, S1.3, S1.4
NetR40_2: R40.2, U8.11
NetR47_1: R47.1, R48.2, U11.2
RX: U2.21, U3.40
SHLD: J8.5, J9.5
SWCLK: J4.4, U3.37
SWDIO: J4.2, U3.36
SWO: J4.6, U3.41
S_IHS_N: R6_IHS.4, R7_IHS.1
S_IHS_P: R6_IHS.3, R9_IHS.1
S_ILS_N: R6_ILS.4, R7_ILS.1
S_ILS_P: R6_ILS.3, R9_ILS.1
TX: U2.20, U3.39
Tamb: C21.2, R19.1, R21.2, U3.30
Tsink: C20.2, R18.1, R20.2, U3.31
VDDPG: R44.1, U9.6, U10.3, U11.4
VDD_CP: C8.2, R11.2, U2.5, U2.6
VDRVPG: R45.2, U3.45, U11.3
VHN: J1.4, R6_IHS.2
VHP: F1.2, J1.3
VHS: L7_VHS.2, U3.15
VLN: C34.2, C35.1, J1.1, R6_ILS.2
VLP: C34.1, C35.2, J1.2, L2.2, R12_VLS.2
VLS: L7_VLS.2, U3.9
V_VHS_P: L7_VHS.1, R13_VHS.1, R49_VHS.1
V_VLS_P: L7_VLS.1, R13_VLS.1, R49_VLS.1
Vb: C22.1, C23.1, C24.1, C25.1, C26.1, C28.1, C32.2, C33.2, C36.2, C37.2, C38.2, C64.2, L1.1, Q1.D, R12_VHS.2, R25.2, R26.2, U8.3
Vcan: C43.2, C44.2, D8.2, J8.1, J9.1, R28.2, U7.2
Vdd: C9.2, C16.2, C17.2, C18.2, C19.2, C31.2, C41.2, C53.2, C60.2, C65.2, C66.2, J4.1, L5.2, R1.2, R14.1, R18.2, R19.2, R45.1, U3.23, U3.35, U3.48, U4.8, U5.7, U6.1, U9.8
Vdda: C2_IHS.2, C2_ILS.2, C12.2, C13.2, C67.2, U1_IHS.3, U1_IHS.7, U1_ILS.3, U1_ILS.7, U3.21, U10.5
Vdds: C42.2, C52.2, C54.2, D6.2, D7.2, R35.2, R44.2, U9.2, U10.1
Vdrv: C56.2, D2.1, D3.1, R47.2, U11.1
Vreg: C45.2, C48.2, C49.2, C50.2, D6.1, L4.2, R33.2, U11.6
Vusb: C5.2, C6.2, D5.1, D7.1, J2.1, U2.7, U2.8
_IHS_N: C4_IHS.2, R10_IHS.2, U1_IHS.5, U3.10
_IHS_P: C1_IHS.2, R8_IHS.2, U1_IHS.4, U3.11
_ILS_N: C4_ILS.2, R10_ILS.2, U1_ILS.5, U3.27
_ILS_P: C1_ILS.2, R8_ILS.2, U1_ILS.4, U3.28
~RST: J4.3, R14.2, U3.7
